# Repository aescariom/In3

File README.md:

# In3
Low cost incubator design.

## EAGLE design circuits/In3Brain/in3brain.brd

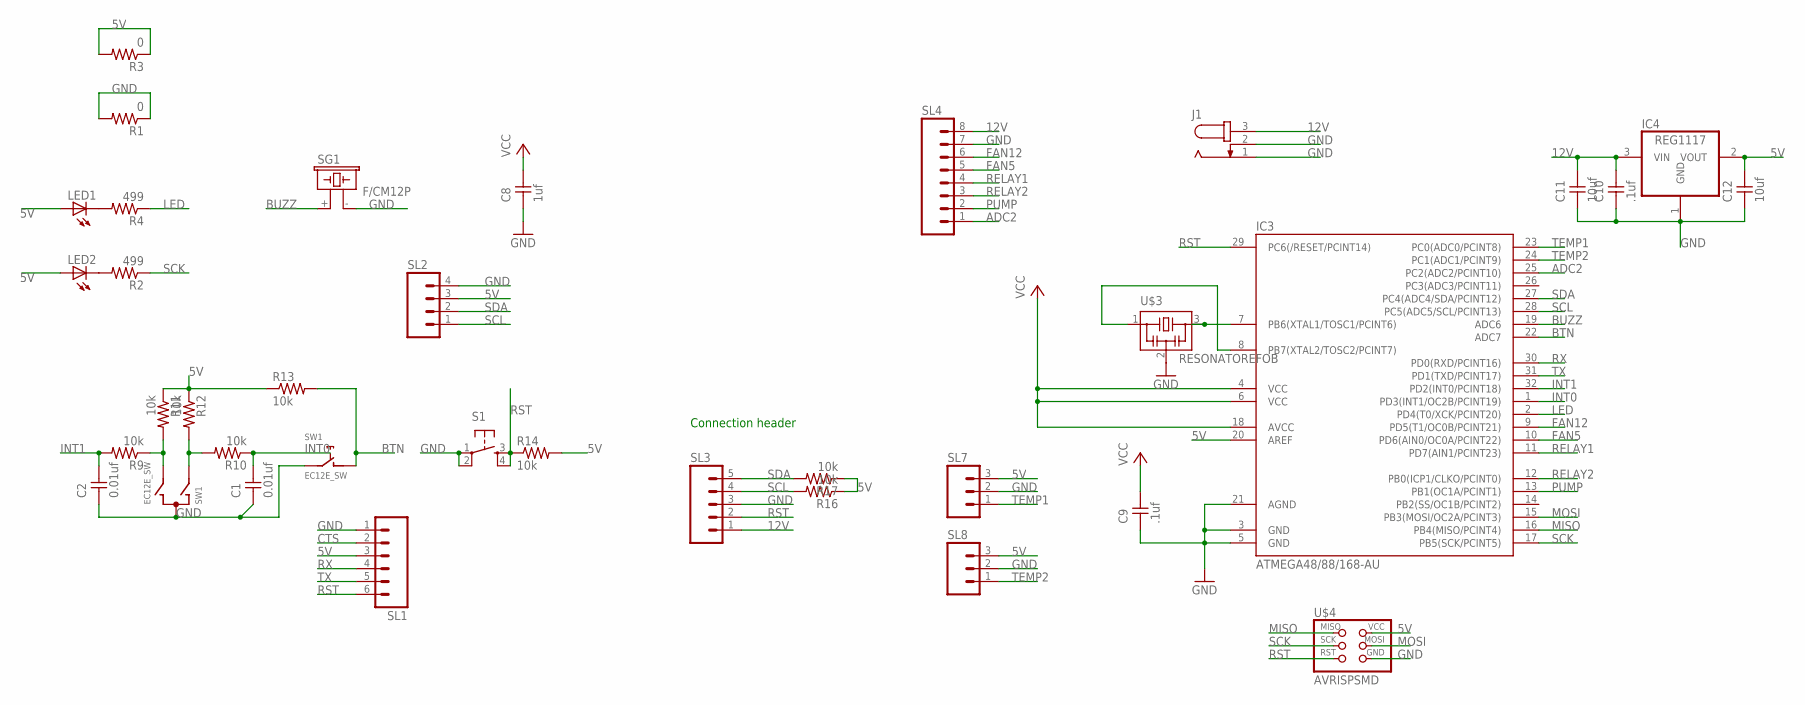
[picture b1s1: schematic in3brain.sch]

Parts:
C1, C2: 0.01uf; 1206
C8: 1uf; 1206
C9, C10: .1uf; 1206
C11, C12: 10uf; 1206
IC3: ATMEGA48/88/168-AU; TQFP32-08
IC4: REG1117; SOT223
J1: JACK-PLUG1; SPC4078
LED1, LED2: LED_E; LED_1206
R1, R3: 0; 1206
R2, R4: 499; 1206
R9, R10, R11, R12, R13, R14, R16, R17: 10k; 1206
S1: 6MM_SWITCH6MM_SWITCH; 6MM_SWITCH
SG1: F/CM12P
SL1: MA06; 06PA
SL2: MA04; 04PA
SL3: MA05; 05PA
SL4: MA08; 08PA
SL7, SL8: MA03; 03P
SW1: EC12E_SW; ALPS_EC12E_SW
U$3: RESONATOREFOB; EFOBM
U$4: AVRISPSMD; 2X03SMD

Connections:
5V: C8.2, C9.2, C12.2, IC3.4 (VCC), IC3.6 (VCC), IC3.18 (AVCC), IC3.20 (AREF), IC4.2 (VOUT), LED1.A, LED2.A, R3.1, R3.2, R11.1, R12.1, R13.1, R14.2, R16.1, R17.1, SL1.3, SL2.3, SL7.3, SL8.3, U$4.2 (VCC)
12V: C10.2, C11.2, IC4.3 (VIN), J1.3, SL3.1, SL4.8
ADC2: IC3.25 (PC2(ADC2/PCINT10)), SL4.1
BTN: IC3.22 (ADC7), R13.2, SW1.D (1)
BUZZ: IC3.19 (ADC6), SG1.+ (1)
CTS: SL1.2
FAN5: IC3.10 (PD6(AIN0/OC0A/PCINT22)), SL4.5
FAN12: IC3.9 (PD5(T1/OC0B/PCINT21)), SL4.6
GND: C1.1, C2.1, C8.1, C9.1, C10.1, C11.1, C12.1, IC3.3 (GND), IC3.5 (GND), IC3.21 (AGND), IC4.1 (GND), J1.1, J1.2, R1.1, R1.2, S1.1, S1.2 (P1), SG1.- (2), SL1.1, SL2.4, SL3.3, SL4.7, SL7.2, SL8.2, SW1.C, SW1.E (2), U$3.2, U$4.6 (GND)
INT0: C1.2, IC3.1 (PD3(INT1/OC2B/PCINT19)), R10.1
INT1: C2.2, IC3.32 (PD2(INT0/PCINT18)), R9.2
LED: IC3.2 (PD4(T0/XCK/PCINT20)), R4.1
MISO: IC3.16 (PB4(MISO/PCINT4)), U$4.1 (MISO)
MOSI: IC3.15 (PB3(MOSI/OC2A/PCINT3)), U$4.4 (MOSI)
unnamed: LED1.C, R4.2
unnamed: LED2.C, R2.2
unnamed: IC3.8 (PB7(XTAL2/TOSC2/PCINT7)), U$3.1
unnamed: IC3.7 (PB6(XTAL1/TOSC1/PCINT6)), U$3.3
unnamed: R9.1, R11.2, SW1.B
unnamed: R10.2, R12.2, SW1.A
PUMP: IC3.13 (PB1(OC1A/PCINT1)), SL4.2
RELAY1: IC3.11 (PD7(AIN1/PCINT23)), SL4.4
RELAY2: IC3.12 (PB0(ICP1/CLKO/PCINT0)), SL4.3
RST: IC3.29 (PC6(/RESET/PCINT14)), R14.1, S1.3 (S), S1.4 (S1), SL1.6, SL3.2, U$4.5 (RST)
RX: IC3.30 (PD0(RXD/PCINT16)), SL1.4
SCK: IC3.17 (PB5(SCK/PCINT5)), R2.1, U$4.3 (SCK)
SCL: IC3.28 (PC5(ADC5/SCL/PCINT13)), R16.2, SL2.1, SL3.4
SDA: IC3.27 (PC4(ADC4/SDA/PCINT12)), R17.2, SL2.2, SL3.5
TEMP1: IC3.23 (PC0(ADC0/PCINT8)), SL7.1
TEMP2: IC3.24 (PC1(ADC1/PCINT9)), SL8.1
TX: IC3.31 (PD1(TXD/PCINT17)), SL1.5

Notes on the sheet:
Connection header

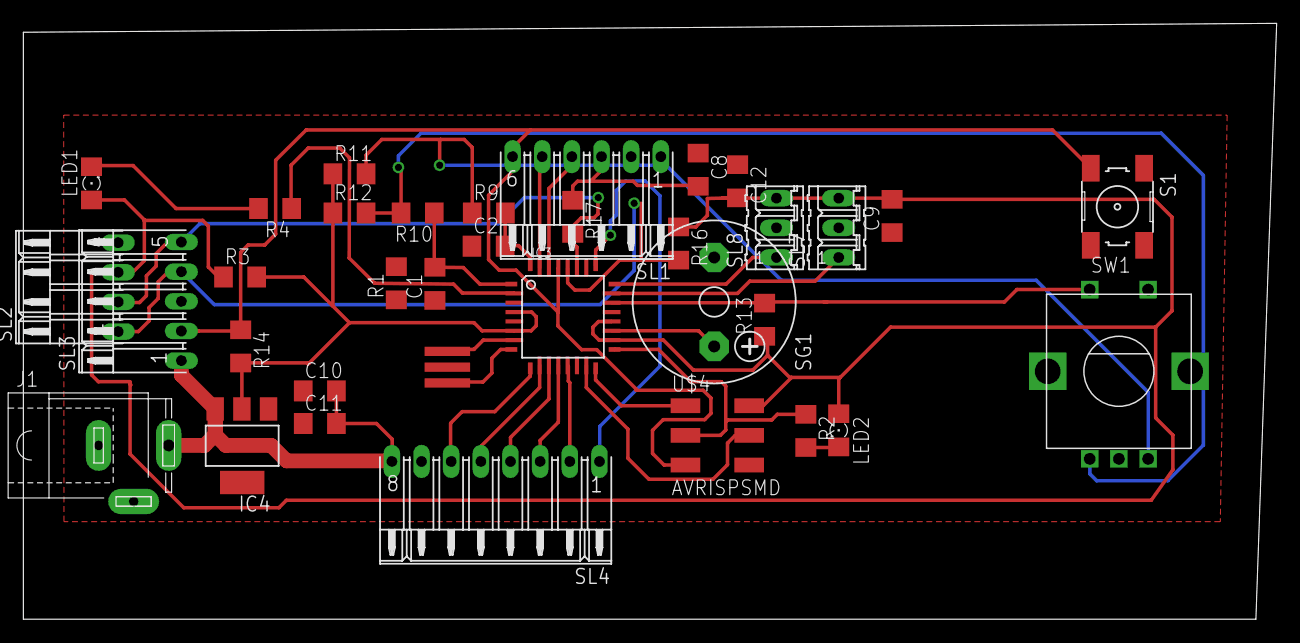
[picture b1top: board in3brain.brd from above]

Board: 2 copper layers, 107.4 x 51.0 mm, 35 parts (0 on the bottom side), 30 nets.

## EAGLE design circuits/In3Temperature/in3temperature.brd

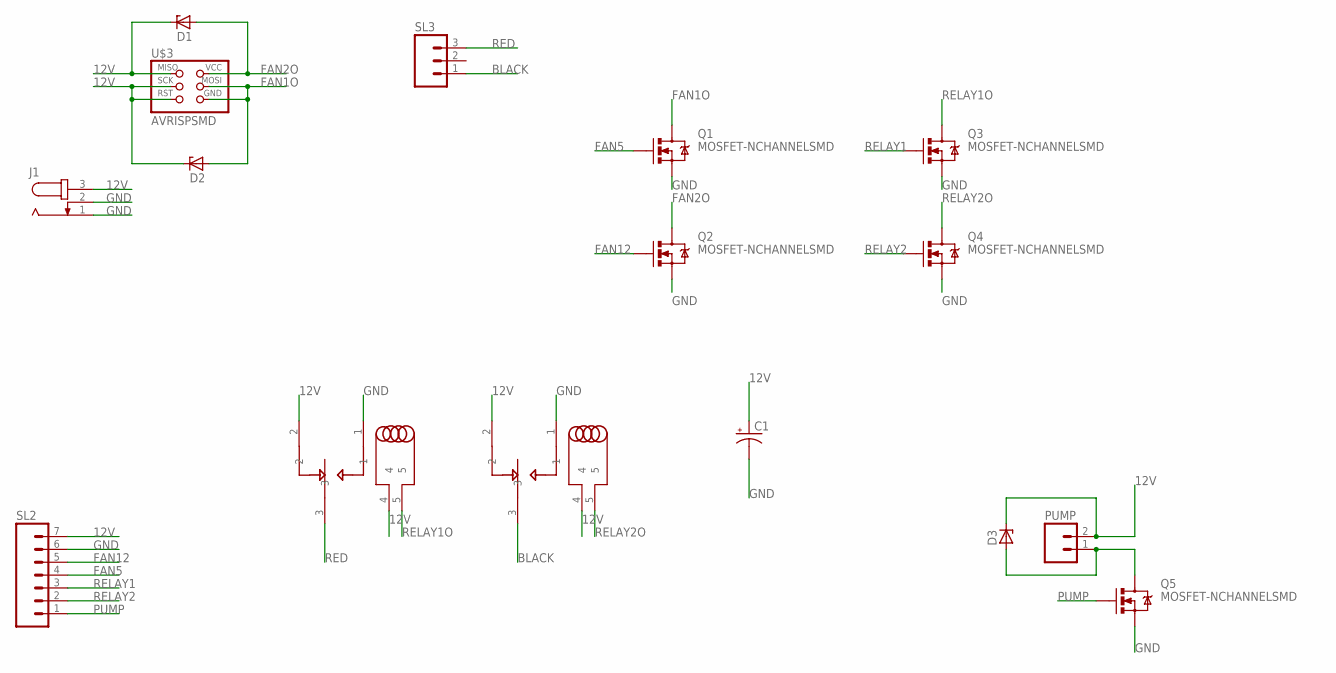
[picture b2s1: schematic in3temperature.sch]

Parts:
C1: CPOL-USE2.5-5; E2,5-5
D1, D2, D3: ZENER_DIODESOD123; SOD123
J1: JACK-PLUG1; SPC4078
PUMP: MA02; 02PA
Q1, Q2, Q3, Q4, Q5: MOSFET-NCHANNELSMD; SOT23-3
SL2: MA07; 07PA
SL3: MA03; 03P
U$1, U$2: RELAY-V23092THROUGH_HOLE; RELAY-V23092
U$3: AVRISPSMD; 2X03SMD

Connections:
12V: C1.+, D1.CATHODE, D2.CATHODE, D3.CATHODE, J1.3, PUMP.2, SL2.7, U$1.2, U$1.4, U$2.2, U$2.4, U$3.1 (MISO), U$3.3 (SCK), U$3.5 (RST)
BLACK: SL3.1, U$2.3
FAN1O: D2.ANODE, Q1.3 (D), U$3.4 (MOSI), U$3.6 (GND)
FAN2O: D1.ANODE, Q2.3 (D), U$3.2 (VCC)
FAN5: Q1.1 (G), SL2.4
FAN12: Q2.1 (G), SL2.5
GND: C1.-, J1.1, J1.2, Q1.2 (S), Q2.2 (S), Q3.2 (S), Q4.2 (S), Q5.2 (S), SL2.6, U$1.1, U$2.1
unnamed: D3.ANODE, PUMP.1, Q5.3 (D)
PUMP: Q5.1 (G), SL2.1
RED: SL3.3, U$1.3
RELAY1: Q3.1 (G), SL2.3
RELAY1O: Q3.3 (D), U$1.5
RELAY2: Q4.1 (G), SL2.2
RELAY2O: Q4.3 (D), U$2.5

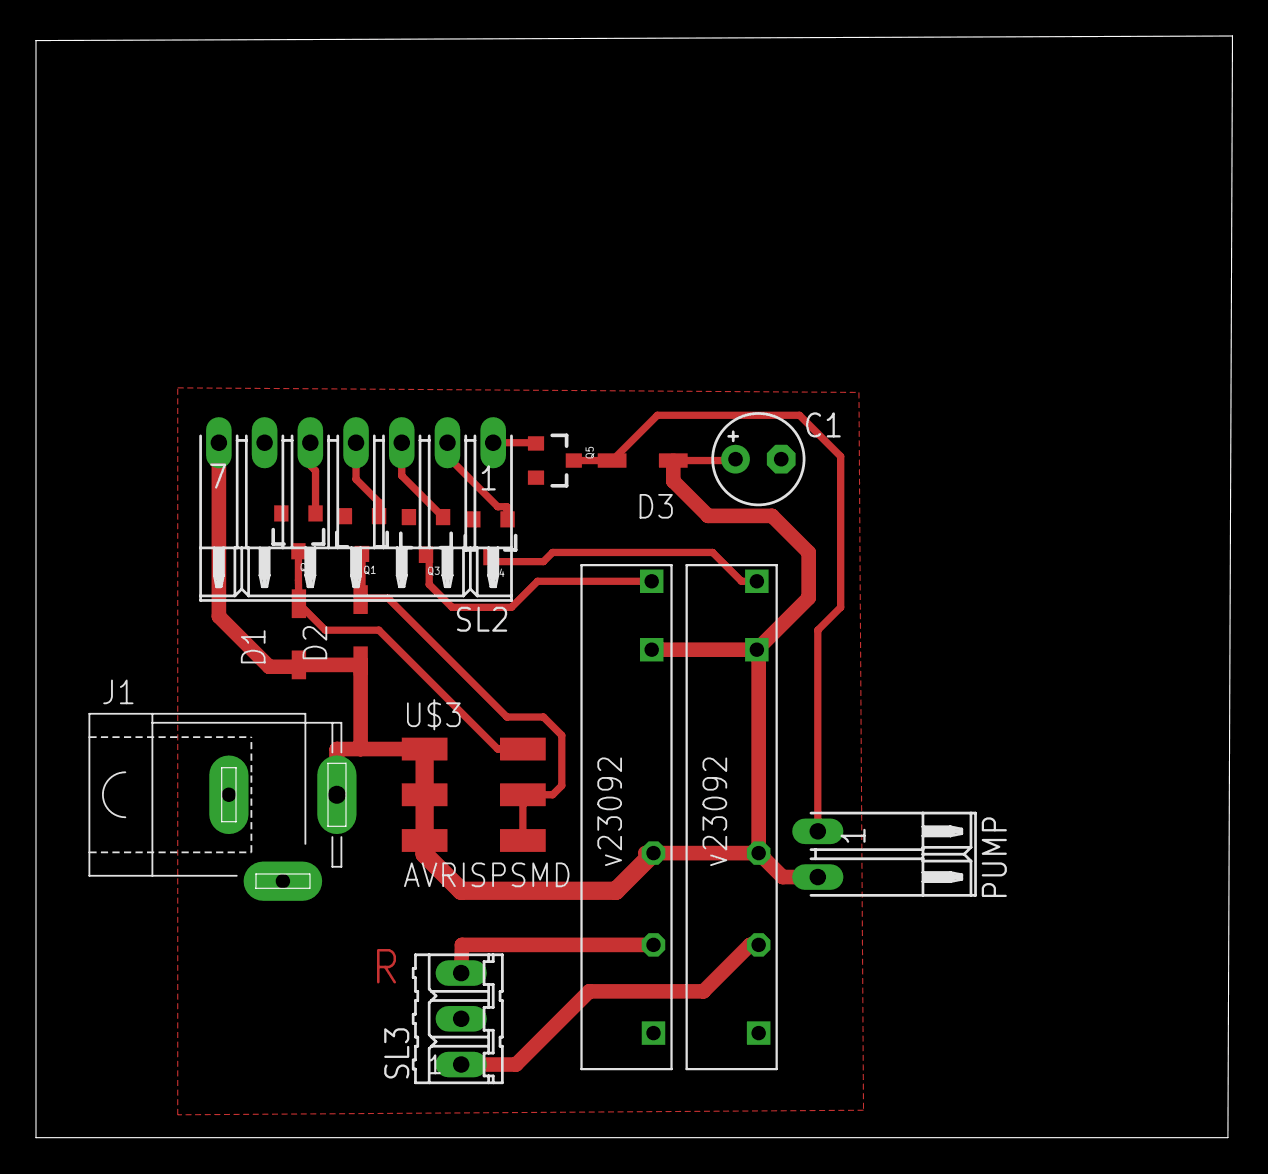
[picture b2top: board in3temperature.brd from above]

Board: 2 copper layers, 66.5 x 61.2 mm, 16 parts (0 on the bottom side), 14 nets.

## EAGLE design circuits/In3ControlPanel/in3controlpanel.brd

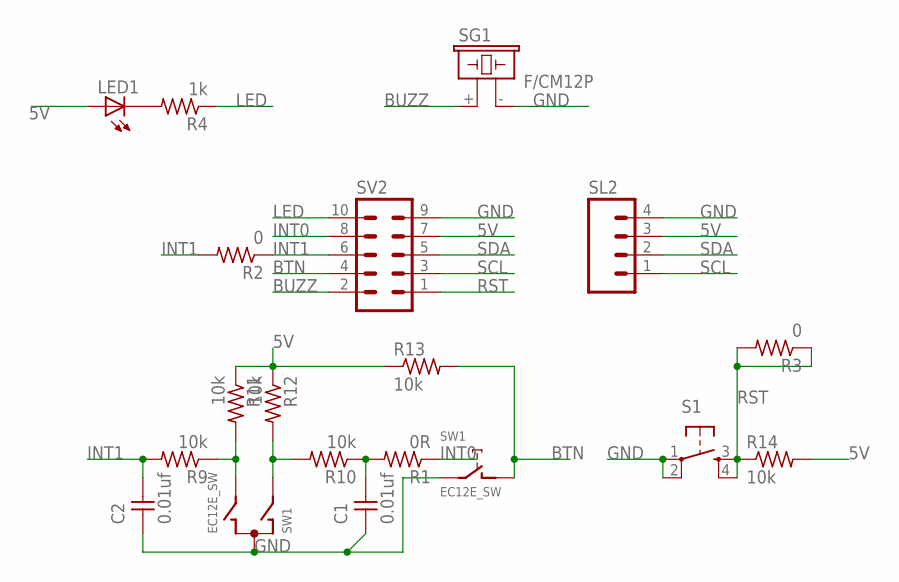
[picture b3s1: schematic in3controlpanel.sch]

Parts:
C1, C2: 0.01uf; 1206
LED1: LED_E; LED_1206
R1: 0R; 1206
R2, R3: 0; 1206
R4: 1k; 1206
R9, R10, R11, R12, R13, R14: 10k; 1206
S1: 6MM_SWITCH6MM_SWITCH; 6MM_SWITCH
SG1: F/CM12P
SL2: MA04; 04PA
SV2: MA05-2
SW1: EC12E_SW; ALPS_EC12E_SW

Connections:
5V: LED1.A, R11.1, R12.1, R13.1, R14.2, SL2.3, SV2.7
BTN: R13.2, SV2.4, SW1.D (1)
BUZZ: SG1.+ (1), SV2.2
GND: C1.1, C2.1, S1.1, S1.2 (P1), SG1.- (2), SL2.4, SV2.9, SW1.C, SW1.E (2)
INT0: C1.2, R1.1, R1.2, R10.1, SV2.8
INT1: C2.2, R2.1, R2.2, R9.2, SV2.6
LED: R4.1, SV2.10
unnamed: LED1.C, R4.2
unnamed: R9.1, R11.2, SW1.B
unnamed: R10.2, R12.2, SW1.A
RST: R3.1, R3.2, R14.1, S1.3 (S), S1.4 (S1), SV2.1
SCL: SL2.1, SV2.3
SDA: SL2.2, SV2.5

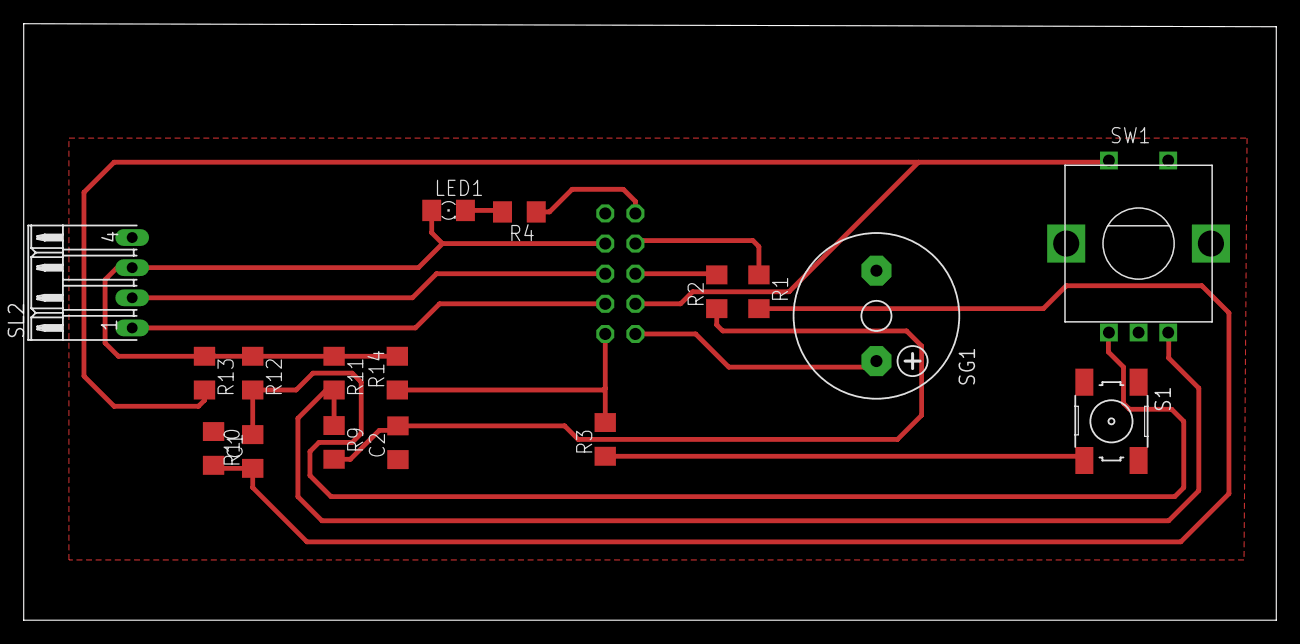
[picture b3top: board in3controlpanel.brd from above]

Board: 2 copper layers, 105.6 x 50.3 mm, 18 parts (1 on the bottom side), 13 nets.

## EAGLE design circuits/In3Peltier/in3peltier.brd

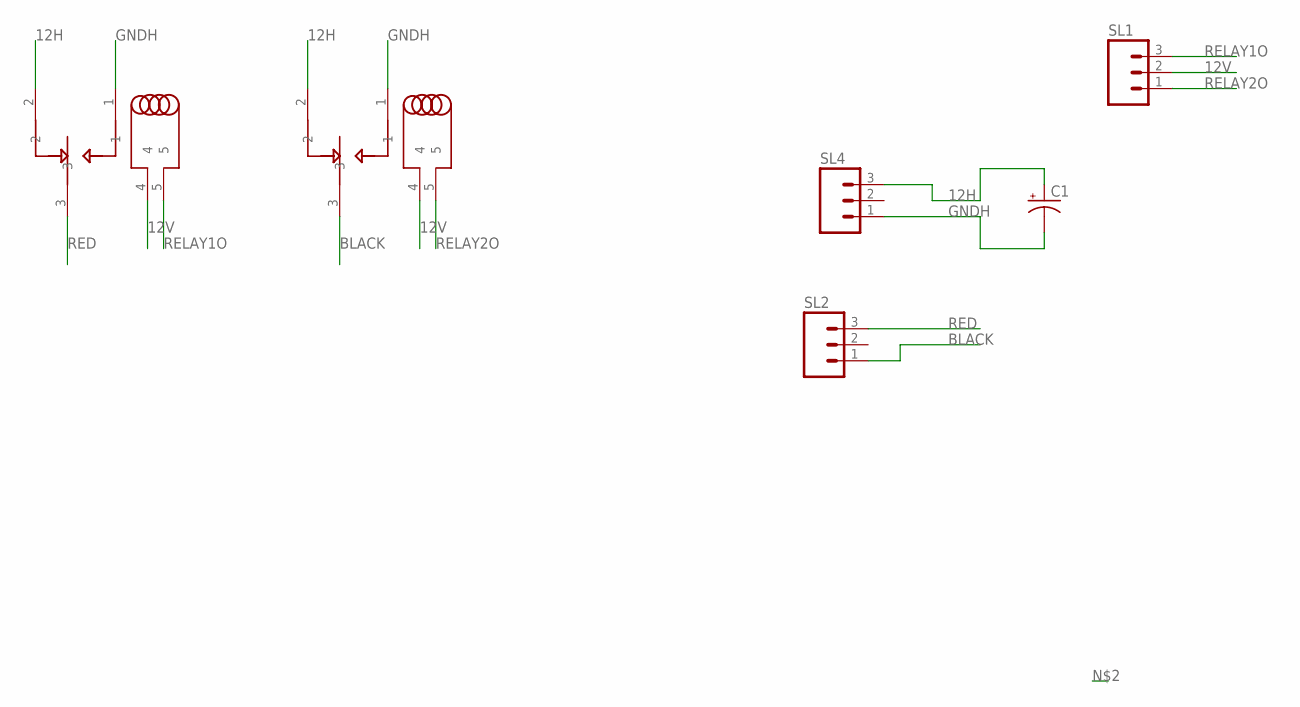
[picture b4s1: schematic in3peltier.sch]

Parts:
C1: CAP_POLPTH2; CPOL-RADIAL-10UF-25V
SL1, SL2, SL4: MA03; 03P
U$1, U$2: RELAY-V23092THROUGH_HOLE; RELAY-V23092

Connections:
12H: C1.1 (+), SL4.3, U$1.2, U$2.2
12V: SL1.2, U$1.4, U$2.4
BLACK: SL2.1, U$2.3
GNDH: C1.2 (-), SL4.1, U$1.1, U$2.1
RED: SL2.3, U$1.3
RELAY1O: SL1.3, U$1.5
RELAY2O: SL1.1, U$2.5

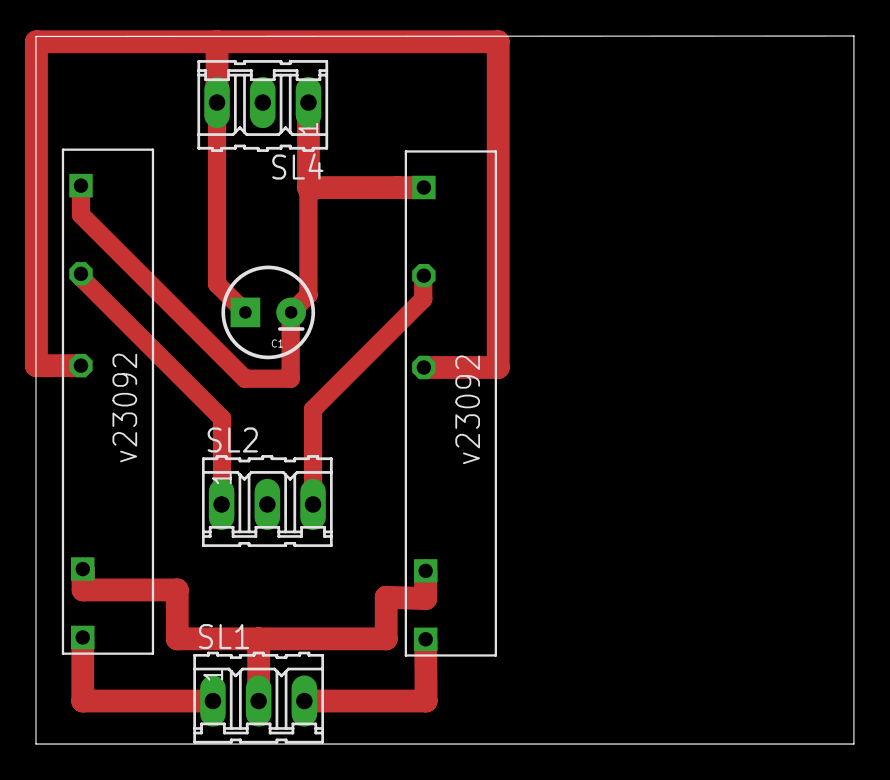
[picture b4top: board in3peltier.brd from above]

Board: 2 copper layers, 45.4 x 39.3 mm, 6 parts (0 on the bottom side), 7 nets.

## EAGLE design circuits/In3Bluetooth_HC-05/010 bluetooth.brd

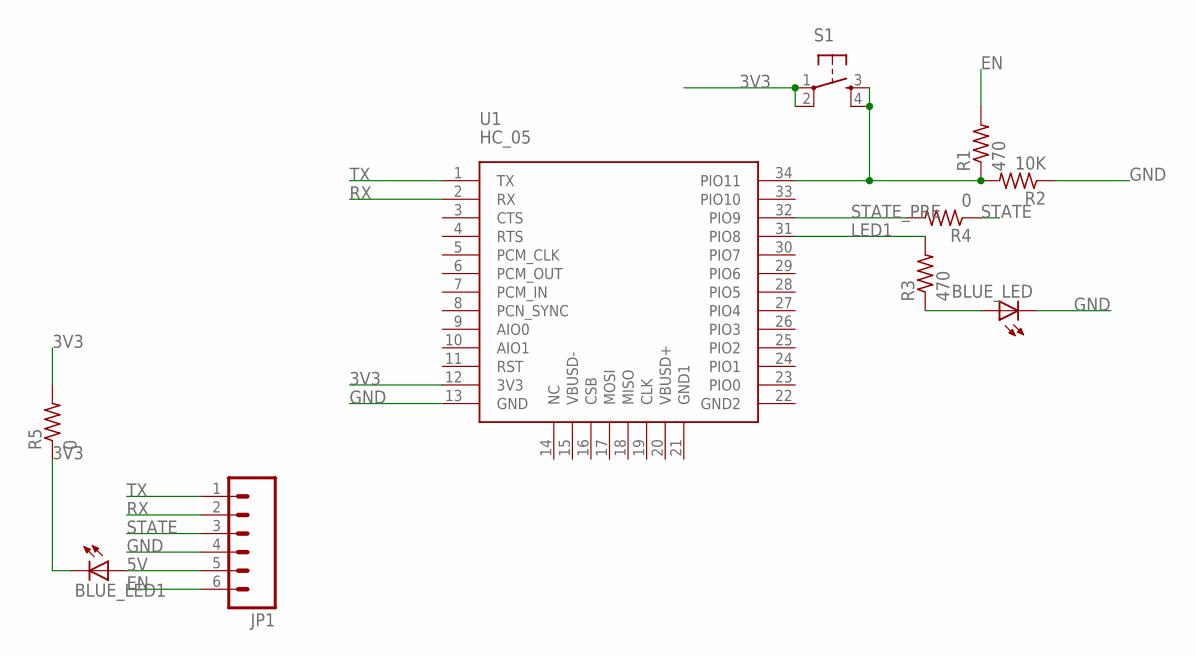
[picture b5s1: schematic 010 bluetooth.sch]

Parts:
BLUE_LED, BLUE_LED1: LED1206; 1206
JP1: M06LONGPADS; 1X06_LONGPADS
R1, R3: 470; 1206
R2: 10K; 1206
R4, R5: 0; 1206
S1: 6MM_SWITCH6MM_SWITCH; 6MM_SWITCH
U1: HC_05; BLUETOOTH_SMD

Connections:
3V3: BLUE_LED1.2 (C), R5.1, R5.2, S1.1, S1.2 (P1), U1.12 (3V3)
5V: BLUE_LED1.1 (A), JP1.5
EN: JP1.6, R1.2
GND: BLUE_LED.2 (C), JP1.4, R2.1, U1.13 (GND)
LED1: R3.2, U1.31 (PIO8)
unnamed: R1.1, R2.2, S1.3 (S), S1.4 (S1), U1.34 (PIO11)
unnamed: BLUE_LED.1 (A), R3.1
RX: JP1.2, U1.2 (RX)
STATE: JP1.3, R4.1
STATE_PRE: R4.2, U1.32 (PIO9)
TX: JP1.1, U1.1 (TX)

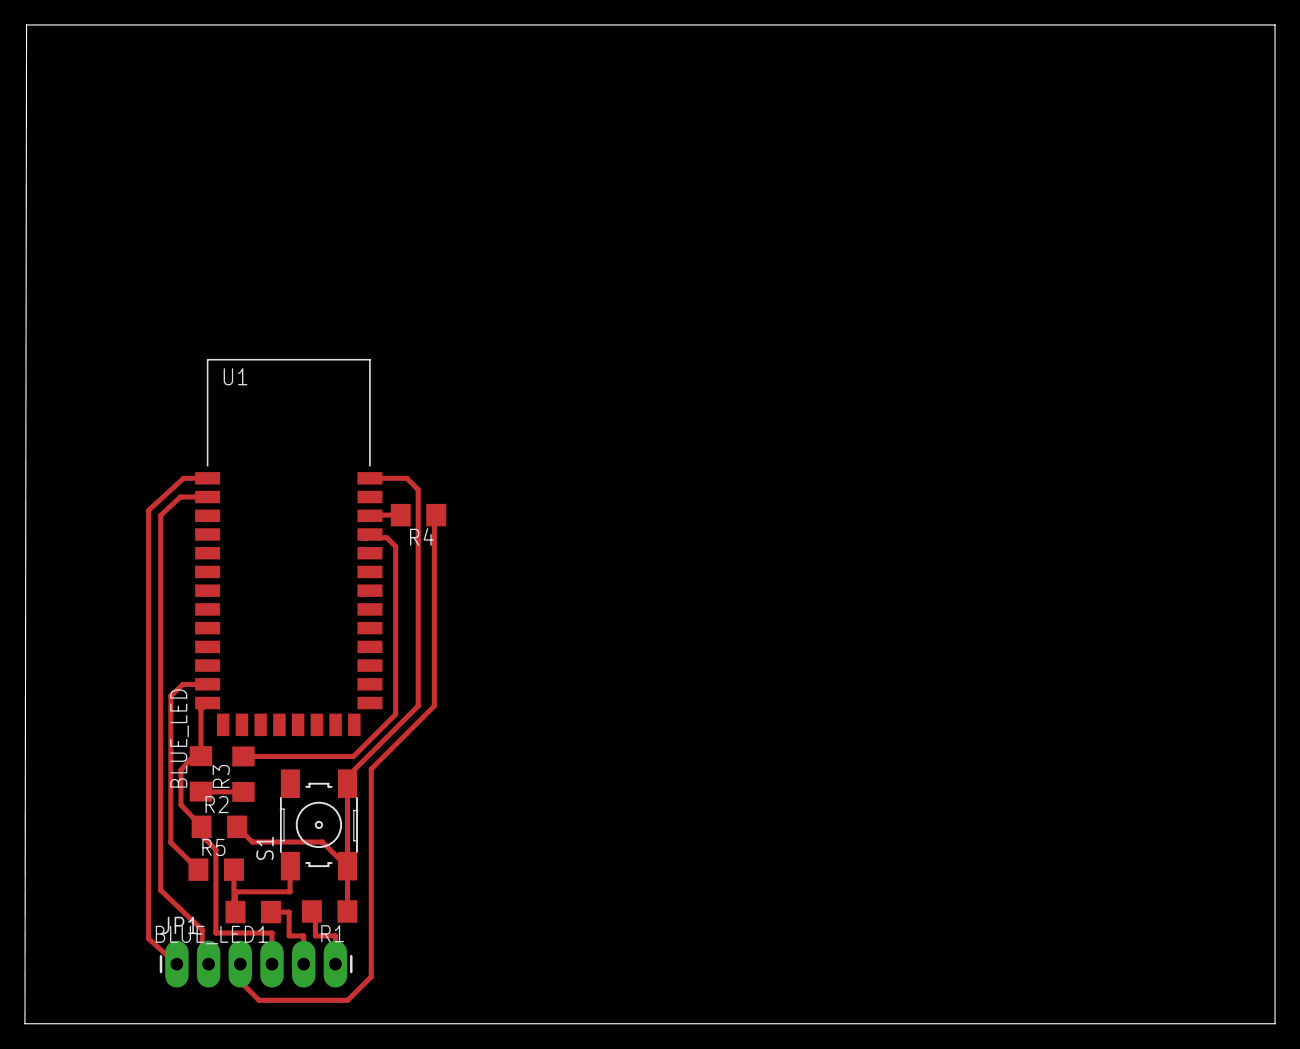
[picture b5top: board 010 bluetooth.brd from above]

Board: 2 copper layers, 100.1 x 80.0 mm, 10 parts (0 on the bottom side), 11 nets.

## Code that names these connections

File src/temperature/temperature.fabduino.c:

/********************************************************
*
*  i2cslave.fabduino.c
* 
*  Alejandro Escario Méndez
*   03/05/2015  
* 
*  (c) Massachusetts Institute of Technology 2015
*  Permission granted for experimental and personal use;
*  license for commercial sale available from MIT.
*********************************************************/

#include <avr/io.h>
#include <util/delay.h>
#include <util/twi.h>
#include <avr/interrupt.h>
#include <stdlib.h>

#include "../lib/output/fan.h"
#include "../lib/output/relay.h"
#include "../lib/operators/new.h"

#include "../lib/output/led.h"

#define output(directions,pin) (directions |= pin) // set port direction for output
#define input(directions,pin) (directions &= (~pin)) // set port direction for input
#define set(port,pin) (port |= pin) // set port pin
#define clear(port,pin) (port &= (~pin)) // clear port pin
#define pin_test(pins,pin) (pins & pin) // test for port pin
#define bit_test(byte,bit) (byte & (1 << bit)) // test for bit set

#define TWI_FREQ 100000L
#define CPU_FREQ 16000000L

#define DHT_DIR DDRD
#define DHT_PORT PORTD
#define DHT_SENS PD3 // PD4
#define DHT_PIN PIND

#define PUMP PD0
#define PUMP_DIRECTION DDRD
#define PUMP_PORT PORTD

#define LED_DIRECTION DDRB
#define LED_PORT PORTB
#define LED_PIN (1 << PB5)

#define DHT_TIMEOUT 200

unsigned char my_addr = 0x28;
unsigned char regaddr, regdata;

Fan* fan1;
Fan* fan2;
Relay* relay1;
Relay* relay2;
Led* led;

volatile int8_t temperature, humidity, targetTemp;

void i2c_init_slave(){
    TWAR = my_addr;
    TWDR = 0x00;
    // SCL freq = F_CPU/(16+2(TWBR)*prescalerValue)
	TWBR = 72;
    //TWBR = 72;  // Bit rate
    TWSR = (0 << TWPS1) | (0 << TWPS0); // Setting prescalar bits
    TWCR = (1<<TWINT) | (1<<TWEA) | (1<<TWEN) | (1<<TWIE);    // get ACK, en TWI, clear int flag
}

int8_t dht_gettemperaturehumidity(int8_t *temperature, int8_t *humidity, volatile uint8_t *port, volatile uint8_t *pin, volatile uint8_t *dir, uint8_t mask) {
	uint8_t bits[5] = {0};
	uint8_t i,j = 0;

	*dir |= (1<<mask);
	*port |= (1<<mask);
	_delay_ms(100);
	*port &= ~(1<<mask);
	_delay_ms(18);
	*port |= (1<<mask);
	*dir &= ~(1<<mask);
	_delay_us(40);
	if((*pin & (1<<mask))) {
		return -1;
	}
	_delay_us(80);
	if(!(*pin & (1<<mask))) {
		return -1;
	}
	_delay_us(80);
	uint16_t timeoutcounter = 0;
	for (j=0; j<5; j++) {
		uint8_t result=0;
		for(i=0; i<8; i++) {
			timeoutcounter = 0;
			while(!(*pin & (1<<mask))) {
				timeoutcounter++;
				if(timeoutcounter > DHT_TIMEOUT) {
					return -1;
				}
			}
			_delay_us(30);
			if(*pin & (1<<mask))
				result |= (1<<(7-i));
			timeoutcounter = 0;
			while(*pin & (1<<mask)) {
				timeoutcounter++;
				if(timeoutcounter > DHT_TIMEOUT) {
					return -1;
				}
			}
		}
		bits[j] = result;
	}
	
	if ((uint8_t)(bits[0] + bits[1] + bits[2] + bits[3]) == bits[4]) {
		*temperature = bits[2];
		*humidity = bits[0];
		return 0;
	}

	return -1;
}

ISR(TWI_vect){
  static unsigned char state = 0, lastVal = 0;
  // Disable Global Interrupt
  cli();
  switch(TW_STATUS){
    case TW_START:  // 0x08
    case TW_REP_START: // 0x10
    case TW_MT_SLA_ACK: // 0x18
    case TW_MT_SLA_NACK: // 0x20
    case TW_MT_DATA_ACK: // 0x28
    case TW_MT_DATA_NACK: // 0x30
    case TW_MR_SLA_ACK:   // 0x40
    case TW_MR_SLA_NACK:   // 0x48
    case TW_MR_DATA_ACK:  // 0x50
    case TW_MR_DATA_NACK:  //  0x58
    case TW_ST_ARB_LOST_SLA_ACK:  //  0xB0
    case TW_SR_ARB_LOST_SLA_ACK: //  0x68
    case TW_SR_GCALL_ACK:    //0x70
    case TW_SR_ARB_LOST_GCALL_ACK:  //  0x78
    case TW_SR_GCALL_DATA_ACK:   // 0x90
    case TW_SR_GCALL_DATA_NACK:  //  0x98
    case TW_NO_INFO:   // 0xF8
      TWCR |= (1<<TWINT);    // Clear TWINT Flag
      break;
    case TW_SR_SLA_ACK:      // 0x60: SLA+W received, ACK returned
      TWCR |= (1<<TWINT);    // Clear TWINT Flag
      break;
    case TW_SR_DATA_ACK:     // data received
      state = TWDR;
      if(lastVal == 'S'){
      	targetTemp = state;
      	state = 0;
      }
      lastVal = state;
      TWCR |= (1<<TWINT);    // Clear TWINT Flag
      break;
    case TW_SR_STOP:         // 0xA0: stop or repeated start condition received while selected
      TWCR |= (1<<TWINT);    // Clear TWINT Flag
      break;
    case TW_ST_SLA_ACK:      // 0xA8: SLA+R received, ACK returned
    	if(state == 'T'){
    		TWDR = temperature;           // Fill TWDR register whith the data to be sent 
      	}else if(state == 'H'){
      		TWDR = humidity;
      	}else{
      		TWDR = 0;
      	}
      TWCR = ((1 << TWEA) | (1 << TWINT) | (1 << TWEN) | (1 << TWIE));   // Enable TWI, Clear TWI interrupt flag
      break;
    case TW_ST_DATA_ACK:     // 0xB8: data transmitted, ACK received
      TWCR |= (1<<TWINT);    // Clear TWINT Flag
      break;
    case TW_ST_DATA_NACK:    // 0xC0: data transmitted, NACK received
      TWCR |= (1<<TWINT);    // Clear TWINT Flag
      break;
    case TW_ST_LAST_DATA:    // 0xC8: last data byte transmitted, ACK received
    case TW_BUS_ERROR:       // 0x00: illegal start or stop condition
    default:
      TWCR |= (1<<TWINT);    // Clear TWINT Flag
      break;
  }

  sei();
}

void turnOnFans(){
  OCR0A=255;
  OCR0B=255;
}

void turnOffFanB(){
  OCR0B=0;
}

void turnOffFans(){
  OCR0A=0;
  OCR0B=0;
}

void init(){
	fan1 = new Fan(&PORTD, &DDRD, PD6);
	fan2 = new Fan(&PORTD, &DDRD, PD5);
    relay1 = new Relay(&PORTD, &DDRD, PD1);
    relay2 = new Relay(&PORTD, &DDRD, PD2);
    led = new Led(&PORTB, &DDRB, PB5);
	
	fan1->init();
	fan2->init();
	relay1->init();
	relay2->init();
    led->init();
}

void heat(){
	relay1->open();
   	relay2->close();
}

void cool(){
	relay2->open();
   	relay1->close();
}

int main() {
	int8_t temperature1, humidity1;
	int8_t temperature2, humidity2;

	init();

   	i2c_init_slave();
   	sei();
   	
   	DDRD   |= (1 << PD5);
   	DDRD   |= (1 << PD6);
   	
    PORTD = 0x00;
    // Initial TIMER0 Fast PWM
    // Fast PWM Frequency = fclk / (N * 256), Where N is the Prescaler
    // f_PWM = 11059200 / (64 * 256) = 675 Hz
    TCCR0A = 0b10100011; // Fast PWM 8 Bit, Clear OCA0/OCB0 on Compare Match, Set on TOP
    TCCR0B = 0b00000011; // Used 64 Prescaler
    TCNT0 = 0;           // Reset TCNT0
    OCR0A = 0;           // Initial the Output Compare register A & B
    OCR0B = 0;
    OCR0A=0;	// Initial Duty Cycle for Channel A
    OCR0B=0;	// Initial Duty Cycle for Channel B
    
    int i = 0;
   	while (1){
  		if(dht_gettemperaturehumidity(&temperature1, &humidity1, &PORTD, &PIND, &DDRD, PD3) != 0){
   			temperature1 = -1;
            humidity1 = -1;
   		}
   		if(dht_gettemperaturehumidity(&temperature2, &humidity2, &PORTD, &PIND, &DDRD, PD4) != 0){
   			temperature2 = -1;
            humidity2 = -1;
   		}
   		if(temperature1 == -1 && temperature2 == -1){
   			temperature = -1;
   		}else if(temperature1 == -1){
   			temperature = temperature2;
   		}else if(temperature2 == -1){
   			temperature = temperature1;
   		}else{
   			temperature = (temperature1 + temperature2) / 2;
   		}
   		if(humidity1 == -1 && humidity2 == -1){
   			humidity = -1;
   		}else if(humidity1 == -1){
   			humidity = humidity2;
   		}else if(humidity2 == -1){
   			humidity = humidity1;
   		}else{
   			humidity = (humidity1 + humidity2) / 2;
   		}
   		
   		if(targetTemp > temperature){
	     	turnOnFans();
	     	heat();
     	}else if(targetTemp < temperature){
	     	turnOnFans();
	     	cool();
     	}else{
     		turnOffFanB();
     	}
   }
}

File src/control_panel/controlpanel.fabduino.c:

/********************************************************
*
*  controlpanel.fabduino.c
* 
*  Alejandro Escario Méndez
*   03/05/2015  
*
*  MIT license
*********************************************************/

#include <avr/io.h> // AVR ctes

#include <util/delay.h>
#include <stdio.h>
#include <avr/pgmspace.h>
#include <avr/interrupt.h>

#include "../lib/output/led.h"
#include "../lib/output/rgb.h"
#include "../lib/output/lcd.h"

#include "../lib/input/switch.h"
#include "../lib/input/rotary.h"

#include "../lib/network/i2c/i2cSlave.h"

LCD* lcd;
Led* led_sck;
Switch* sw_rotary;
RGB* rgb;

volatile unsigned char auxTargetTemperature = 0;
volatile unsigned char targetTemperature = 36;
volatile bool changeTargetTemp = false;
volatile unsigned char temperature = 0;
volatile unsigned char humidity = 0;

unsigned char my_addr = 0x28;

volatile unsigned char menuOpt = 1;
volatile bool menuEnabled = false;
volatile bool temperatureMenu = false;

//Menu Strings
const char MENU[2][20] = {
							"%c <<Back>>",
							"%c Change temp"
						};

void init(){
	led_sck = new Led(&PORTB, &DDRB, PB5);
	sw_rotary = new Switch(&PORTD, &DDRD, &PIND, PD4);
	rgb = new RGB(&PORTC, &DDRC, &PINC, PC1, PC0, PC2);
	lcd = new LCD();
	lcd->setDb7(&PORTB, &DDRB, PB2);
	lcd->setDb6(&PORTB, &DDRB, PB1);
	lcd->setDb5(&PORTB, &DDRB, PB0);
	lcd->setDb4(&PORTD, &DDRD, PD7);
	lcd->setE(&PORTD, &DDRD, PD6);
	lcd->setRs(&PORTD, &DDRD, PD5);
	
	led_sck->init();
	sw_rotary->init();
	rgb->init();
	lcd->init();
	lcd->erase();
	lcd->cursorOff();
	initRotary();
	i2c_init_slave();
}

void freeAll(){
	delete(led_sck);
	delete(sw_rotary);
	delete(rgb);
	delete(lcd);
}

void printVars(){
	char line[16];
	sprintf(line, "Temp.: %2i/%2i%cC", temperature, targetTemperature, 0b11011111);
	lcd->println(line, 1);
	sprintf(line, "Humidity: %3i%%", humidity);
	lcd->println(line, 2);
}

void printMenu(){
	
	char line[16];
	sprintf(line, MENU[0], menuOpt == 0 ? '>' : ' ');
	lcd->println(line, 1);
	sprintf(line, MENU[1], menuOpt == 1 ? '>' : ' ');
	lcd->println(line, 2);
}

void printChangingTargetTemperature(){
	char line[16];
	sprintf(line, "%2i%cC", auxTargetTemperature, 0b11011111);
	lcd->println(line, 2);
}

void printTemperatureMenu(){
	lcd->println("Set new value:", 1);
	auxTargetTemperature = targetTemperature;
	printChangingTargetTemperature();
}

void menuAction(volatile unsigned char opt){
	switch(opt){
		case 0:
			lcd->erase();
			printVars();
			menuEnabled = false;
			temperatureMenu = false;
			break;
		case 1:
			lcd->erase();
			printTemperatureMenu();
			menuEnabled = false;
			temperatureMenu = true;
			break;
	}
}

int main(void) {
	long lastEncoderValue = 0;
	
	init();
	
	while(1){
		if(menuEnabled){
			if(lastEncoderValue < encoderValue){
				++menuOpt;
			}else if(lastEncoderValue > encoderValue){
				--menuOpt;
			}
			if(lastEncoderValue != encoderValue){
				menuOpt %= 2;
				printMenu();
				lastEncoderValue = encoderValue;
			}
			if(sw_rotary->isPressed()){
				menuAction(menuOpt);
			}
		}else if(temperatureMenu){
		
			if(lastEncoderValue < encoderValue){
				++auxTargetTemperature;
			}else if(lastEncoderValue > encoderValue){
				--auxTargetTemperature;
			}
			if(auxTargetTemperature == 255){
				auxTargetTemperature = 0;
			}else if(auxTargetTemperature > 50){
				auxTargetTemperature = 50;
			}
			
			if(lastEncoderValue != encoderValue){
				printChangingTargetTemperature();
				lastEncoderValue = encoderValue;
			}
			if(sw_rotary->isPressed()){
				targetTemperature = auxTargetTemperature;
				changeTargetTemp = true;
				lcd->erase();
				printVars();
				menuEnabled = false;
				temperatureMenu = false;
			}
		}else{
			if(sw_rotary->isPressed()){
				menuOpt = 0;
				lcd->erase();
				printMenu();
				menuEnabled = true;
				temperatureMenu = false;
				lastEncoderValue = encoderValue;
			}else{
				printVars();
			}
		}
		if(temperature > targetTemperature){
			rgb->turnOnBlue();
		}else if(temperature == targetTemperature){
			rgb->turnOnGreen();
		}else{
			rgb->turnOnRed();
		}
		
	}
	
	freeAll();
}

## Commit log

2015-07-16 In3 v1.0
    Version 1.0 of the incubator. The same that has been designed during
    FabAcademy 2015
2015-09-20 Inner 12V fan speed changed
2015-09-20 Air flow
    Air flow 3D printed pieces.
    All of them can be printed without supports.
2015-09-20 Axis mold files. Once the mold is made, a piece can be done in 5 minutes
2015-09-20 Structure update to v1.1.
    More stable and strong legs. Less cut time
2015-09-20 Assembling documentation
2016-01-18 Electronics v2
2016-11-03 License
2017-02-27 New Electronics
2017-07-06 new electronics: less components, less bards, space optimization and some software error fixes
2017-07-15 Circuit error fix & improved temperature selector

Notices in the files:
parts and their libraries:
01_SparkFun: Licensing: CC v3.0 Share-Alike You are welcome to use this library for commercial purposes.
